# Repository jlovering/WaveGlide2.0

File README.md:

# WaveGlide 2.0

This project extends the work by [Nortd Labs](http://nortd.github.io/WaveGlide/). It seeks to take their work and simpify the board design.

This is intended as an Open Source Hardware ([OSHWA](https://www.oshwa.org)) project and will attempt to follow the OSHWA [Best Practices](https://www.oshwa.org/sharing-best-practices/). All parts of this design are released under CC-BY-SA 4.0 unless otherwise noted. See LICENSE.md for more details.

# Status
This project is in it's infancy. Current status is "Design Incomplete"

## Detailed Status
* EE Design
  * Component Selection: Complete
  * Schematic Capture: Incomplete
    * Power domains remain
  * Board Layout: Incomplete
    * Initial Floorplaning Started
  * Board Validation: Incomplete

* ME Design
  * ECAD Parts: Mostly Complete
  * MCAD Parts: Not Started
  * Assempbly Design: Not Started

 * Software Design: Not Started

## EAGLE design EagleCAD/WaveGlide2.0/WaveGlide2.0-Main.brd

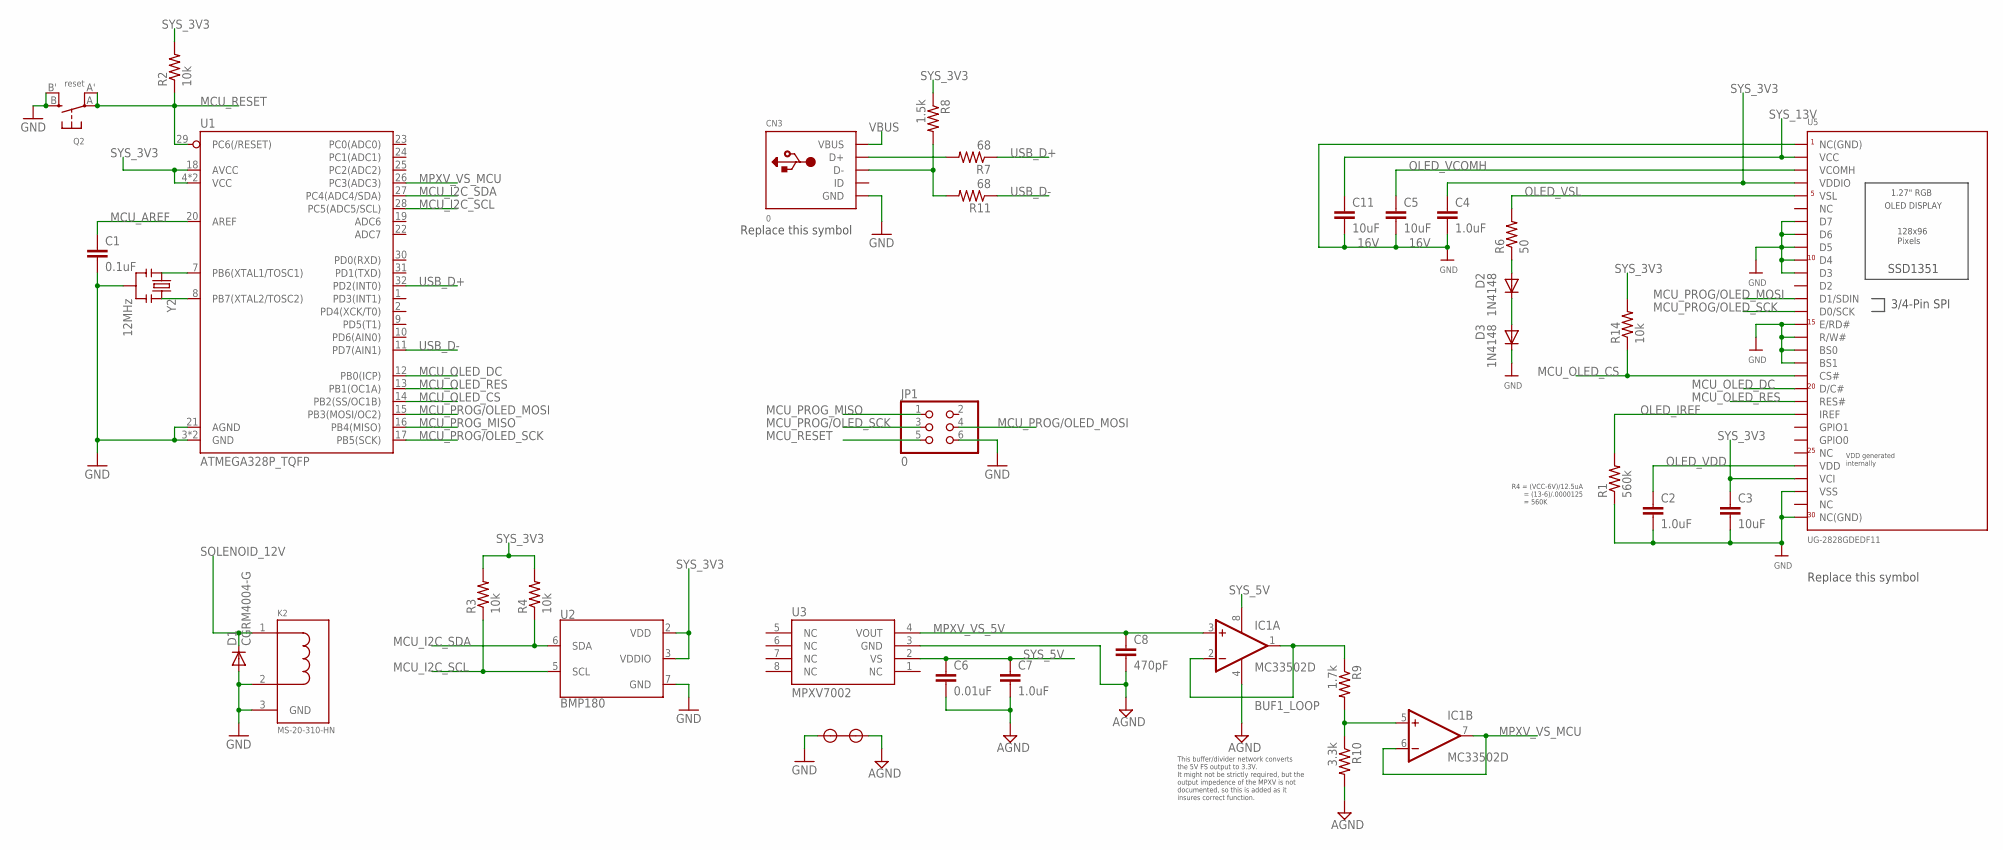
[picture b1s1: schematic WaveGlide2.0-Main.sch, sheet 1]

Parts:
C1: 0.1uF; C0805
C2, C4, C7: 1.0uF; C0805
C3, C5, C11: 10uF; C0805
C6: 0.01uF; C0805
C8: 470pF; C0805
CN3: 0; 4UCONN_20329
D1: CGRM4004-G; SOD-123_MINI-SMA
D2: 1N4148; SOD323-W; MPN MBRD835LT4G
D3: 1N4148; SOD323-W
IC1: MC33502D; SO08
JP1: 0; 2X03
K2: MS-20-310-HN
Q2: reset; BTN_KMR2_4.6X2.8
R1: 560k; R0603
R2, R3, R4, R14: 10k; R0603
R6: 50; R0603
R7, R11: 68; R0603
R8: 1.5k; R0603
R9: 1.7k; R0603
R10: 3.3k; R0603
U1: ATMEGA328P_TQFP; TQFP32-08; MPN TPS55340RTER
U2: BMP180
U3: MPXV7002
U5: UG-2828GDEDF11; FPC_XF2M-3015-1A
U$2: SHORT
Y2: 12MHz; RESONATOR-SMD

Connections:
AGND: C6.2, C7.2, C8.2, IC1.4 (V-), R10.2, U3.3 (GND), U$2.P$2
BUF1_LOOP: IC1.1 (OUT), IC1.2 (-IN), R9.1
D+1: CN3.D+, R7.2
D-1: CN3.D-, R8.2, R11.2
GND: C1.2, C2.2, C3.2, C4.2, C5.2, C11.2, CN3.BASE@1 (GND), CN3.BASE@2 (GND), CN3.GND, CN3.SPRT@1 (GND), CN3.SPRT@2 (GND), CN3.SPRT@3 (GND), CN3.SPRT@4 (GND), D1.A, D3.C, JP1.6, K2.2 (VR), K2.3 (GND), Q2.B (S), Q2.B' (S1), R1.1, U1.3 (GND), U1.5 (GND), U1.21 (AGND), U2.7 (GND), U5.P$1 (NC(GND)), U5.P$3 (VSS), U5.P$13 (BS1), U5.P$14 (BS0), U5.P$15 (R/W#), U5.P$16 (E/RD#), U5.P$20 (D3), U5.P$21 (D4), U5.P$22 (D5), U5.P$23 (D6), U5.P$24 (D7), U5.P$30 (NC(GND)), U$2.P$1, Y2.2; also elsewhere on the board
MCU_AREF: C1.1, U1.20 (AREF)
MCU_I2C_SCL: R3.1, U1.28 (PC5(ADC5/SCL)), U2.5 (SCL)
MCU_I2C_SDA: R4.1, U1.27 (PC4(ADC4/SDA)), U2.6 (SDA)
MCU_OLED_CS: R14.1, U1.14 (PB2(SS/OC1B)), U5.P$12 (CS#)
MCU_OLED_DC: U1.12 (PB0(ICP)), U5.P$11 (D/C#)
MCU_OLED_RES: U1.13 (PB1(OC1A)), U5.P$10 (RES#)
MCU_PROG/OLED_MOSI: JP1.4, U1.15 (PB3(MOSI/OC2)), U5.P$18 (D1/SDIN)
MCU_PROG/OLED_SCK: JP1.3, U1.17 (PB5(SCK)), U5.P$17 (D0/SCK)
MCU_PROG_MISO: JP1.1, U1.16 (PB4(MISO))
MCU_RESET: JP1.5, Q2.A, Q2.A' (P1), R2.1, U1.29 (PC6(/RESET))
MPXV_VS_5V: C8.1, IC1.3 (+IN), U3.4 (VOUT)
MPXV_VS_MCU: IC1.6 (-IN), IC1.7 (OUT), U1.26 (PC3(ADC3))
unnamed: D2.C, D3.A
unnamed: D2.A, R6.1
unnamed: IC1.5 (+IN), R9.2, R10.1
unnamed: U1.7 (PB6(XTAL1/TOSC1)), Y2.1
unnamed: U1.8 (PB7(XTAL2/TOSC2)), Y2.3
OLED_IREF: R1.2, U5.P$9 (IREF)
OLED_VCOMH: C5.1, U5.P$28 (VCOMH)
OLED_VDD: C2.1, U5.P$5 (VDD)
OLED_VSL: R6.2, U5.P$26 (VSL)
SOLENOID_12V: D1.C, K2.1 (VS); also elsewhere on the board
SYS_3V3: C3.1, C4.1, R2.2, R3.2, R4.2, R8.1, R14.2, U1.4 (VCC), U1.6 (VCC), U1.18 (AVCC), U2.2 (VDD), U2.3 (VDDIO), U5.P$4 (VCI), U5.P$27 (VDDIO); also elsewhere on the board
SYS_5V: C6.1, C7.1, IC1.8 (V+), U3.2 (VS); also elsewhere on the board
SYS_13V: C11.1, U5.P$29 (VCC); also elsewhere on the board
USB_D+: R7.1, U1.32 (PD2(INT0))
USB_D-: R11.1, U1.11 (PD7(AIN1))
VBUS: CN3.VBUS

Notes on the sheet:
R4 = (VCC-6V)/12.5uA = (13-6)/.0000125 = 560K
VDD generated internally
This buffer/divider network converts the 5V FS output to 3.3V. It might not be strictly required, but the output impedence of the MPXV is not documented, so this is added as it insures correct function.
Replace this symbol

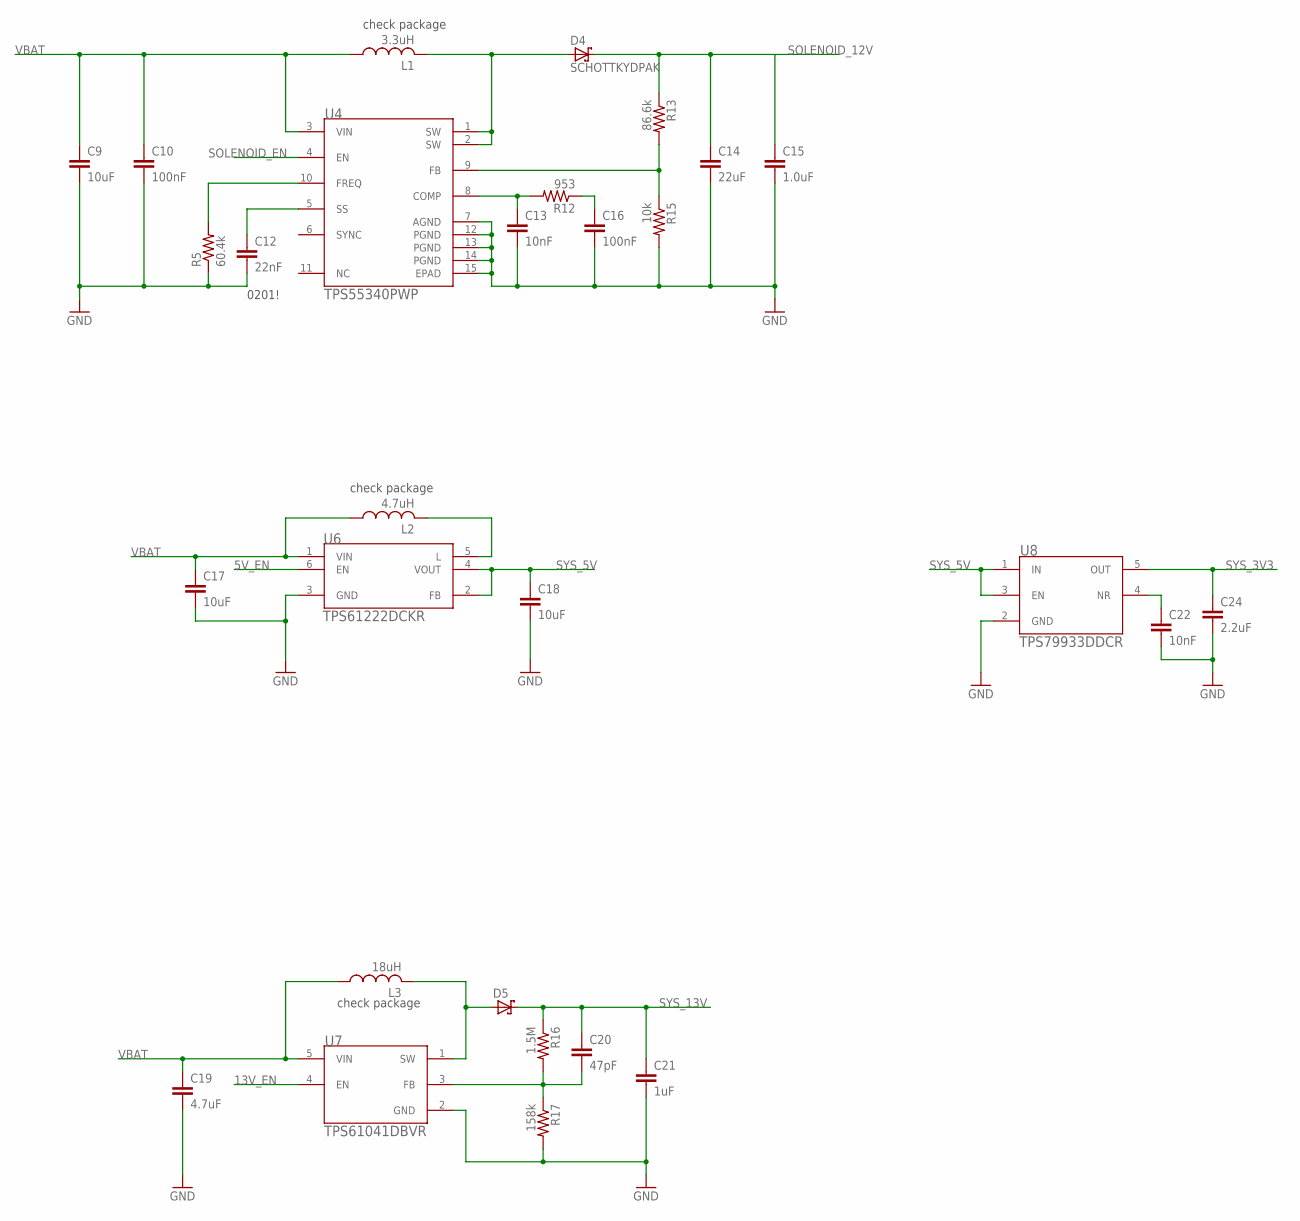
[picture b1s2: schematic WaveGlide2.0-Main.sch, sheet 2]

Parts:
C9: 10uF; C0805; MPN GRM219R61A106KE44D
C10: 100nF; C0805; MPN CC0805KRX7R8BB104
C12: 22nF; C0402; MPN GRM155R60J223KA01D
C13: 10nF; C0805; MPN GCM2195C1H103JA16D
C14: 22uF; C1210; MPN GRM32ER61C226ME20L
C15: 1.0uF; C0805; MPN EMK107B7105KA-T
C16: 100nF; C0805; MPN 08053C104JAZ2A
C17: 10uF; C0805; MPN GRM21BR60J106ME19L
C18: 10uF; C0805; MPN C0805C106K8PACTU
C19: 4.7uF; C0603; MPN GRM188R60J475KE19D
C20: 47pF; C0603; MPN 06035A470KAT2A
C21: 1uF; C0805; MPN GMK212B7105KG
C22: 10nF; C0402; MPN GRM033R70J103KA01D
C24: 2.2uF; C0402; MPN JMK105BJ225MV-F
D4: SCHOTTKYDPAK; D-PAK_TO252AA
D5: SCHOTTKYSOT-123; SOD-123_MINI-SMA
L1: 3.3uH; L4532P; MPN XAL5030-332MEB
L2: 4.7uH; L4035M; MPN LQM2HPN4R7MGCL
L3: 18uH; L4035M; MPN LPS4018-183MRB
R5: 60.4k; R0603; MPN CRCW060360K4FKEA
R12: 953; R0603; MPN CRCW0603953RFKEA
R13: 86.6k; R0603; MPN CRCW060386K6FKEA
R15: 10k; R0805; MPN RR1220P-103-D
R16: 1.5M; R0603; MPN CRCW06031M50FKEA
R17: 158k; R0603; MPN CRCW0603158KFKEA
U4: TPS55340PWP; PWP14
U6: TPS61222DCKR; DCK6
U7: TPS61041DBVR; DBV5
U8: TPS79933DDCR; DDC5

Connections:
5V_EN: U6.6 (EN)
13V_EN: U7.4 (EN)
GND: C9.2, C10.2, C12.2, C13.2, C14.2, C15.2, C16.2, C17.2, C18.2, C19.2, C21.2, C22.2, C24.2, R5.1, R15.2, R17.2, U4.7 (AGND), U4.12 (PGND), U4.13 (PGND), U4.14 (PGND), U4.15 (EPAD), U6.3 (GND), U7.2 (GND), U8.2 (GND); also elsewhere on the board
unnamed: D5.A, L3.2, U7.1 (SW)
SOLENOID_12V: C14.1, C15.1, D4.4 (C), R13.1; also elsewhere on the board
SOLENOID_EN: U4.4 (EN)
SYS_3V3: C24.1, U8.5 (OUT); also elsewhere on the board
SYS_5V: C18.1, U6.2 (FB), U6.4 (VOUT), U8.1 (IN), U8.3 (EN); also elsewhere on the board
SYS_13V: C20.1, C21.1, D5.C, R16.1; also elsewhere on the board
TPS55340_COMP: C13.1, R12.2, U4.8 (COMP)
TPS55340_FB: R13.2, R15.1, U4.9 (FB)
TPS55340_FB1: C20.2, R16.2, R17.1, U7.3 (FB)
TPS55340_FREQ: R5.2, U4.10 (FREQ)
TPS55340_SS: C12.1, U4.5 (SS)
TPS55340_SW: D4.1 (A), D4.3 (A), L1.2, U4.1 (SW), U4.2 (SW)
TPS61222_L: L2.2, U6.5 (L)
TPS66340_COMP1: C16.1, R12.1
TPS79933_NR: C22.1, U8.4 (NR)
VBAT: C9.1, C10.1, C17.1, C19.1, L1.1, L2.1, L3.1, U4.3 (VIN), U6.1 (VIN), U7.5 (VIN)

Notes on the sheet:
0201!
check package

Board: 2 copper layers, 63 parts (10 on the bottom side), 43 nets, no tracks yet.

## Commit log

2018-03-10 Add remote modules
2018-03-10 Docs
2018-03-10 KiCAD CAD
2018-03-10 EagleCAD
2018-03-11 Updated docs and part additions
2018-03-11 Remove backup files from git
2018-03-16 Add OLED ref schematic
2018-03-16 Updated BOM, add more docs
2018-03-16 Updated Schematic
2018-03-16 Add MCAD step files
2018-03-16 Doc reorg and add TI Boost App Note
2018-03-16 Banish DS_Store
2018-03-16 Rearrange Docs, add final power components
2018-03-16 TI Ref designs for power
2018-03-17 Start generating schematic
2018-03-17 AVR Pocket Reference Board
2018-03-17 Update submodules
2018-03-17 Fix DRC unknown net issues
2018-03-18 Add buffer divider network, and floorplanning
2018-03-18 submodule update
2018-03-18 Add license and readme
2018-03-18 Fix license and readme
2018-03-20 Add MacroFAB EDA libraries
2018-03-20 Death to DS_Store
2018-03-20 Add design notes for the 12V boost
2018-03-20 Remove useless ref designs
2018-03-20 Add BOM management
2018-03-20 Ref MCAD for TPS55340
2018-03-20 Add TPS55340 boost circuit
2018-03-20 Death to spaces in paths
2018-03-26 Add 5V regulator
2018-03-26 Add 13V boost for OLED
2018-03-26 Update BOM fix some bad components
2018-03-26 Add 3V3 Regulator
2018-03-27 Add diodes to power regulators
2018-03-27 Floor planning 12V regulator

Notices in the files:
parts and their libraries:
SparkFun: Licensing: CC v3.0 Share-Alike You are welcome to use this library for commercial purposes.
